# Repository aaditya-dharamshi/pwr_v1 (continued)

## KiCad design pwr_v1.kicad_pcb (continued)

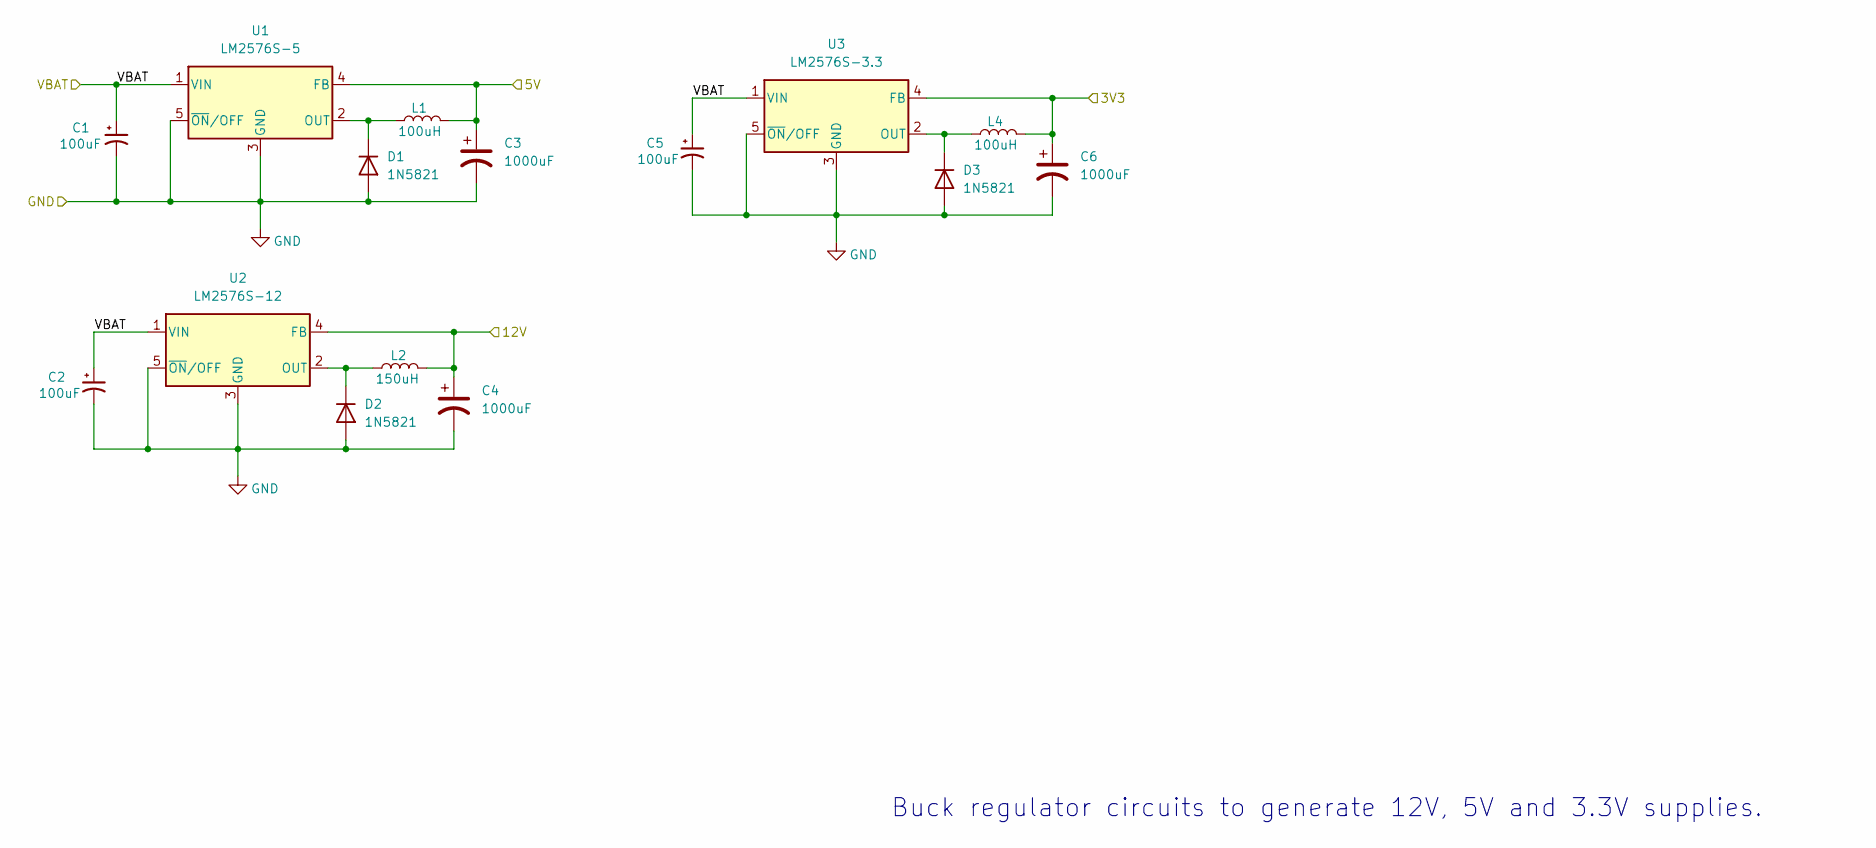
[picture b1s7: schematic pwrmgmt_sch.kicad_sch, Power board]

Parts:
C1, C2, C5: 100uF; CP_Elec_8x10
C3: 1000uF; CP_Elec_8x10.5
C4, C6: 1000uF; CP_Elec_10x10.5
D1, D2, D3: 1N5821; D_DO-201AD_P15.24mm_Horizontal
L1, L4: 100uH; L_Sunlord_MWSA1206S-101
L2: 150uH; L_TaiTech_TMPC1265_13.5x12.5mm
U1: LM2576S-5; TO-263-5_TabPin3
U2: LM2576S-12; TO-263-5_TabPin3
U3: LM2576S-3.3; TO-263-5_TabPin3

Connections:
3V3: C6.1, L4.2, U3.4 (FB); also elsewhere on the board
5V: C3.1, L1.2, U1.4 (FB); also elsewhere on the board
12V: C4.1, L2.2, U2.4 (FB); also elsewhere on the board
GND: C1.2, C2.2, C3.2, C4.2, C5.2, C6.2, D1.2 (A), D2.2 (A), D3.2 (A), U1.3 (GND), U1.5 (~ON/OFF), U2.3 (GND), U2.5 (~ON/OFF), U3.3 (GND), U3.5 (~ON/OFF); also elsewhere on the board
unnamed: D1.1 (K), L1.1, U1.2 (OUT)
unnamed: D2.1 (K), L2.1, U2.2 (OUT)
unnamed: D3.1 (K), L4.1, U3.2 (OUT)
VBAT: C1.1, C2.1, C5.1, U1.1 (VIN), U2.1 (VIN), U3.1 (VIN); also elsewhere on the board

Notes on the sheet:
Buck regulator circuits to generate 12V, 5V and 3.3V supplies.

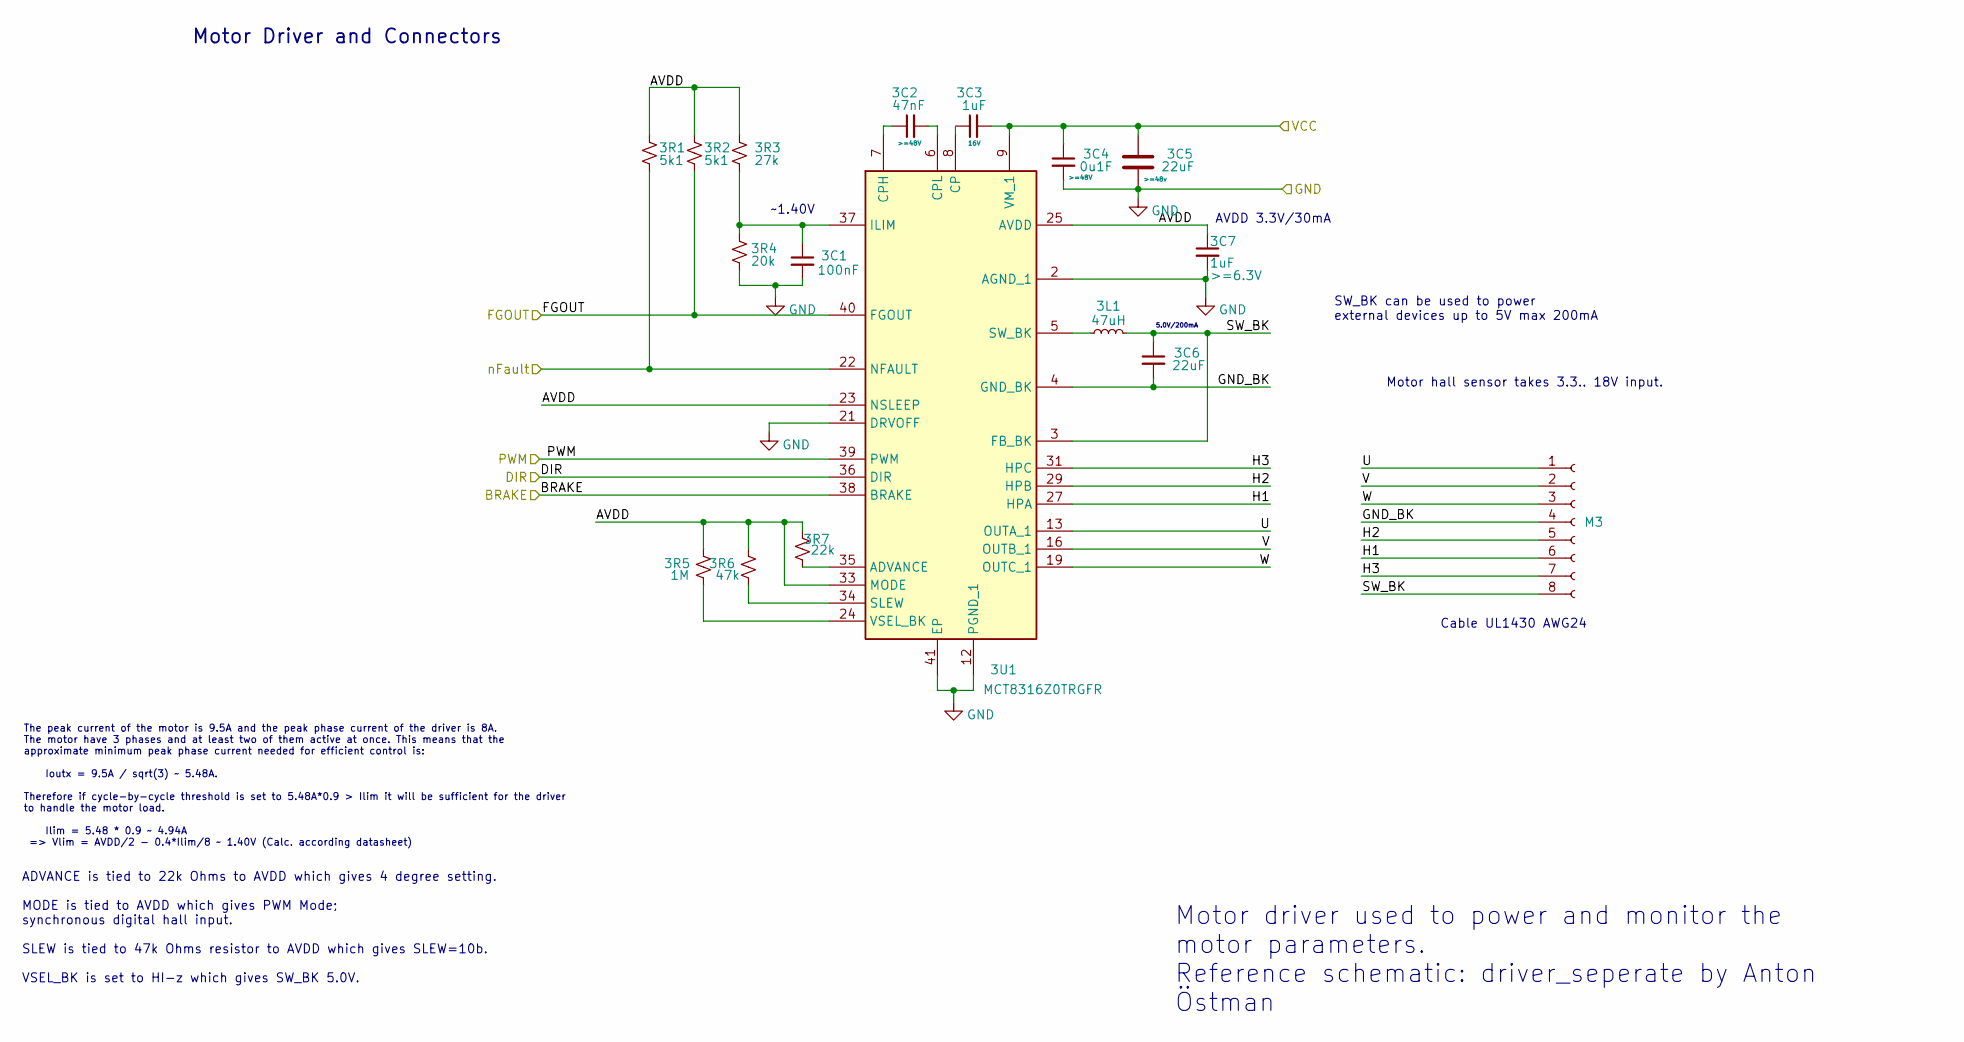
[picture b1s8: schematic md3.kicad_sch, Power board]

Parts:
3C1: 100nF; C_0402_1005Metric
3C2: 47nF; C_0402_1005Metric; Voltage >=48V
3C3: 1uF; C_0402_1005Metric; Voltage 16V
3C4: 0u1F; C_0402_1005Metric; Voltage >=48V
3C5: 22uF; C_2220_5750Metric; Voltage >=48v
3C6: 22uF; C_0402_1005Metric
3C7: 1uF; C_0402_1005Metric; Voltage >=6.3V
3L1: 47uH; L_0805_2012Metric
3R1, 3R2: 5k1; R_0603_1608Metric
3R3: 27k; R_0603_1608Metric
3R4: 20k; R_0603_1608Metric
3R5: 1M; R_0805_2012Metric
3R6: 47k; R_0402_1005Metric
3R7: 22k; R_0402_1005Metric
3U1: MCT8316Z0TRGFR; RGF0040E-IPC_B; Mouser Part Number 595-CT8316Z0TQRGFRQ1
M3: Conn_01x08_Socket; PinHeader_1x08_P2.54mm_Vertical

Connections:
5V: 3R1.2, 3U1.22 (NFAULT); also elsewhere on the board
/MotorDriver3/AVDD: 3C7.1, 3R1.1, 3R2.1, 3R3.1, 3R5.2, 3R6.2, 3R7.2, 3U1.23 (NSLEEP), 3U1.25 (AVDD), 3U1.33 (MODE)
/MotorDriver3/BRAKE: 3U1.38 (BRAKE); also elsewhere on the board
/MotorDriver3/DIR: 3U1.36 (DIR); also elsewhere on the board
/MotorDriver3/FGOUT: 3R2.2, 3U1.40 (FGOUT); also elsewhere on the board
/MotorDriver3/GND_BK: 3C6.2, 3U1.4 (GND_BK), M3.4
/MotorDriver3/H1: 3U1.27 (HPA), M3.6
/MotorDriver3/H2: 3U1.29 (HPB), M3.5
/MotorDriver3/H3: 3U1.31 (HPC), M3.7
/MotorDriver3/PWM: 3U1.39 (PWM); also elsewhere on the board
/MotorDriver3/SW_BK: 3C6.1, 3L1.2, 3U1.3 (FB_BK), M3.8
/MotorDriver3/U: 3U1.13 (OUTA_1), 3U1.14 (OUTA_2), M3.1
/MotorDriver3/V: 3U1.16 (OUTB_1), 3U1.17 (OUTB_2), M3.2
/MotorDriver3/W: 3U1.19 (OUTC_1), 3U1.20 (OUTC_2), M3.3
GND: 3C1.2, 3C4.2, 3C5.2, 3C7.2, 3R4.2, 3U1.2 (AGND_1), 3U1.12 (PGND_1), 3U1.15 (PGND_2), 3U1.18 (PGND_3), 3U1.21 (DRVOFF), 3U1.26 (AGND_2), 3U1.41 (EP); also elsewhere on the board
unnamed: 3R7.1, 3U1.35 (ADVANCE)
unnamed: 3C3.1, 3U1.8 (CP)
unnamed: 3C2.1, 3U1.7 (CPH)
unnamed: 3C2.2, 3U1.6 (CPL)
unnamed: 3C1.1, 3R3.2, 3R4.1, 3U1.37 (ILIM)
unnamed: 3R6.1, 3U1.34 (SLEW)
unnamed: 3L1.1, 3U1.5 (SW_BK)
unnamed: 3R5.1, 3U1.24 (VSEL_BK)
VBAT: 3C3.2, 3C4.1, 3C5.1, 3U1.9 (VM_1), 3U1.10 (VM_2), 3U1.11 (VM_3); also elsewhere on the board

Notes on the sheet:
5.0V/200mA
ADVANCE is tied to 22k Ohms to AVDD which gives 4 degree setting. MODE is tied to AVDD which gives PWM Mode; synchronous digital hall input. SLEW is tied to 47k Ohms resistor to AVDD which gives SLEW=10b. VSEL_BK is set to HI-z which gives SW_BK 5.0V.
Cable UL1430 AWG24
The peak current of the motor is 9.5A and the peak phase current of the driver is 8A. The motor have 3 phases and at least two of them active at once. This means that the approximate minimum peak phase current needed for efficient control is: Ioutx = 9.5A / sqrt(3) ~ 5.48A. Therefore if cycle-by-cy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
Motor hall sensor takes 3.3.. 18V input.
~1.40V
AVDD 3.3V/30mA
SW_BK can be used to power external devices up to 5V max 200mA
Motor Driver and Connectors
Motor driver used to power and monitor the motor parameters. Reference schematic: driver_seperate by Anton Östman

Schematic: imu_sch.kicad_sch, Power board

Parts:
C12, C13: 100nF; C_0402_1005Metric
R2, R3: 1k; R_0603_1608Metric
U4: LSM6DSLTR; LGA-14_3x2.5mm_P0.5mm_LayoutBorder3x4y

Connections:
3V3: C12.1, C13.1, R2.1, R3.1, U4.5 (VDDIO), U4.8 (VDD); also elsewhere on the board
/IMU/CS: U4.12 (CS); also elsewhere on the board
/IMU/INT1: U4.4 (INT1); also elsewhere on the board
/IMU/INT2: U4.9 (INT2); also elsewhere on the board
/IMU/SCL: R2.2, U4.13 (SCL); also elsewhere on the board
/IMU/SDA: R3.2, U4.14 (SDA); also elsewhere on the board
/IMU/SDO_SAO: U4.1 (SDO/SA0); also elsewhere on the board
GND: C12.2, C13.2, U4.2 (SDX), U4.3 (SCX), U4.6 (GND), U4.7 (GND); also elsewhere on the board

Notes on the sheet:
CS-0 : SPI mode CS-1 : I2C mode
IMU unit used to measure various motion parameters. Reference schematic: imu_LSM6DSL by Li Ang Hu

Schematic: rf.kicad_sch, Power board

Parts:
J_RF1: Conn_02x04_Counter_Clockwise; PinSocket_2x04_P2.54mm_Vertical

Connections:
3V3: J_RF1.8; also elsewhere on the board
/RF/CE: J_RF1.2; also elsewhere on the board
/RF/CSN: J_RF1.7; also elsewhere on the board
/RF/IRQ: J_RF1.5; also elsewhere on the board
/RF/MISO: J_RF1.4; also elsewhere on the board
/RF/MOSI: J_RF1.6; also elsewhere on the board
/RF/SCK: J_RF1.3; also elsewhere on the board
GND: J_RF1.1; also elsewhere on the board

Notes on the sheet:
RF Module socket

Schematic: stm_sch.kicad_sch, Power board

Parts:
CN11, CN12: Conn_02x36_Odd_Even; PinHeader_2x36_P2.54mm_Vertical_SMD

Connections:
5V: CN11.6; also elsewhere on the board
/Battery Supervisor/M: CN12.65; also elsewhere on the board
/Battery Supervisor/O1: CN11.11; also elsewhere on the board
/Battery Supervisor/O2: CN11.56; also elsewhere on the board
/Battery Supervisor/O3: CN11.54; also elsewhere on the board
/Battery Supervisor/O4: CN11.9; also elsewhere on the board
/Battery Supervisor/O5: CN12.42; also elsewhere on the board
/Battery Supervisor/O6: CN11.38; also elsewhere on the board
/STM32/CE_NRF: CN12.4; also elsewhere on the board
/STM32/CS_NRF: CN12.3; also elsewhere on the board
/STM32/IR_CS: CN11.30; also elsewhere on the board
/STM32/IR_IN: CN12.12; also elsewhere on the board
/STM32/IR_INT1: CN12.35; also elsewhere on the board
/STM32/IR_INT2: CN12.37; also elsewhere on the board
/STM32/IR_OUT: CN12.14; also elsewhere on the board
/STM32/KICKER_CHARGE: CN12.18; also elsewhere on the board
/STM32/KICKER_CS: CN12.49; also elsewhere on the board
/STM32/KICKER_DISCHARGE1: CN12.25; also elsewhere on the board
/STM32/KICKER_DISCHARGE2: CN12.16; also elsewhere on the board
/STM32/KICKER_ERR: CN12.30; also elsewhere on the board
/STM32/MISO: CN12.13; also elsewhere on the board
/STM32/MOSI: CN12.29; also elsewhere on the board
/STM32/MOTOR1_BREAK: CN12.22; also elsewhere on the board
/STM32/MOTOR1_ENCODER: CN11.4; also elsewhere on the board
/STM32/MOTOR1_PWM: CN12.52; also elsewhere on the board
/STM32/MOTOR1_REVERSE: CN12.17; also elsewhere on the board
/STM32/MOTOR2_BREAK: CN12.41; also elsewhere on the board
/STM32/MOTOR2_ENCODER: CN12.64; also elsewhere on the board
/STM32/MOTOR2_PWM: CN12.56; also elsewhere on the board
/STM32/MOTOR2_REVERSE: CN12.40; also elsewhere on the board
/STM32/MOTOR3_BREAK: CN12.43; also elsewhere on the board
/STM32/MOTOR3_ENCODER: CN11.32; also elsewhere on the board
/STM32/MOTOR3_PWM: CN12.55; also elsewhere on the board
/STM32/MOTOR3_REVERSE: CN12.44; also elsewhere on the board
/STM32/MOTOR4_BREAK: CN11.46; also elsewhere on the board
/STM32/MOTOR4_ENCODER: CN11.28; also elsewhere on the board
/STM32/MOTOR4_PWM: CN12.51; also elsewhere on the board
/STM32/MOTOR4_REVERSE: CN12.53; also elsewhere on the board
/STM32/MOTOR5_BREAK: CN11.62; also elsewhere on the board
/STM32/MOTOR5_ENCODER: CN11.17; also elsewhere on the board
/STM32/MOTOR5_PWM: CN11.50; also elsewhere on the board
/STM32/MOTOR5_REVERSE: CN11.48; also elsewhere on the board
/STM32/NRF_IRQ: CN12.26; also elsewhere on the board
/STM32/SCK: CN12.11; also elsewhere on the board
GND: CN11.8, CN11.19, CN11.20, CN11.22, CN11.49, CN11.60, CN12.9, CN12.20, CN12.39, CN12.54, CN12.63; also elsewhere on the board

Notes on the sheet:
STM32 Nucleo H755ZI devboard connector
Nucleo pin mapping details

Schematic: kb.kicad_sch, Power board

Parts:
J1: Conn_01x12_Pin; CON12_1X12_UR_DF13
Q1: BSS84; SOT-23
RK1, RK2, RK3, RK4, RK5, RK6, RK7, RK8: 100; R_0402_1005Metric
RK9, RK10: 10k; R_0402_1005Metric

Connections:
3V3: J1.10, RK9.1, RK10.1; also elsewhere on the board
12V: J1.11; also elsewhere on the board
/KB/CHG: RK5.2; also elsewhere on the board
/KB/CLK: RK2.2; also elsewhere on the board
/KB/CS: Q1.1 (G), RK1.2; also elsewhere on the board
/KB/DIS1: RK6.2, RK9.2; also elsewhere on the board
/KB/DIS2: RK7.2, RK10.2; also elsewhere on the board
/KB/ERR: RK8.2; also elsewhere on the board
/KB/MISO: Q1.3 (D); also elsewhere on the board
/KB/MOSI: RK4.2; also elsewhere on the board
GND: J1.9; also elsewhere on the board
unnamed: J1.1, RK1.1
unnamed: J1.2, RK2.1
unnamed: J1.3, RK3.1
unnamed: J1.4, RK4.1
unnamed: J1.5, RK5.1
unnamed: J1.6, RK6.1
unnamed: J1.7, RK7.1
unnamed: J1.8, RK8.1
unnamed: Q1.2 (S), RK3.2
VBAT: J1.12; also elsewhere on the board

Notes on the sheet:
Kicker board connector

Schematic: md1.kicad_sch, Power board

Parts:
1C1: 100nF; C_0402_1005Metric
1C2: 47nF; C_0402_1005Metric; Voltage >=48V
1C3: 1uF; C_0402_1005Metric; Voltage 16V
1C4: 0u1F; C_0402_1005Metric; Voltage >=48V
1C5: 22uF; C_2220_5750Metric; Voltage >=48v
1C6: 22uF; C_0402_1005Metric
1C7: 1uF; C_0402_1005Metric; Voltage >=6.3V
1L1: 47uH; L_0805_2012Metric
1R1, 1R2: 5k1; R_0603_1608Metric
1R3: 27k; R_0603_1608Metric
1R4: 20k; R_0603_1608Metric
1R5: 1M; R_0805_2012Metric
1R6: 47k; R_0402_1005Metric
1R7: 22k; R_0402_1005Metric
1U1: MCT8316Z0TRGFR; RGF0040E-IPC_B; Mouser Part Number 595-CT8316Z0TQRGFRQ1
M1: Conn_01x08_Socket; PinHeader_1x08_P2.54mm_Vertical

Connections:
5V: 1R1.2, 1U1.22 (NFAULT); also elsewhere on the board
/MotorDriver1/AVDD: 1C7.1, 1R1.1, 1R2.1, 1R3.1, 1R5.2, 1R6.2, 1R7.2, 1U1.23 (NSLEEP), 1U1.25 (AVDD), 1U1.33 (MODE)
/MotorDriver1/BRAKE: 1U1.38 (BRAKE); also elsewhere on the board
/MotorDriver1/DIR: 1U1.36 (DIR); also elsewhere on the board
/MotorDriver1/FGOUT: 1R2.2, 1U1.40 (FGOUT); also elsewhere on the board
/MotorDriver1/GND_BK: 1C6.2, 1U1.4 (GND_BK), M1.4
/MotorDriver1/H1: 1U1.27 (HPA), M1.6
/MotorDriver1/H2: 1U1.29 (HPB), M1.5
/MotorDriver1/H3: 1U1.31 (HPC), M1.7
/MotorDriver1/PWM: 1U1.39 (PWM); also elsewhere on the board
/MotorDriver1/SW_BK: 1C6.1, 1L1.2, 1U1.3 (FB_BK), M1.8
/MotorDriver1/U: 1U1.13 (OUTA_1), 1U1.14 (OUTA_2), M1.1
/MotorDriver1/V: 1U1.16 (OUTB_1), 1U1.17 (OUTB_2), M1.2
/MotorDriver1/W: 1U1.19 (OUTC_1), 1U1.20 (OUTC_2), M1.3
GND: 1C1.2, 1C4.2, 1C5.2, 1C7.2, 1R4.2, 1U1.2 (AGND_1), 1U1.12 (PGND_1), 1U1.15 (PGND_2), 1U1.18 (PGND_3), 1U1.21 (DRVOFF), 1U1.26 (AGND_2), 1U1.41 (EP); also elsewhere on the board
unnamed: 1R7.1, 1U1.35 (ADVANCE)
unnamed: 1C3.1, 1U1.8 (CP)
unnamed: 1C2.1, 1U1.7 (CPH)
unnamed: 1C2.2, 1U1.6 (CPL)
unnamed: 1C1.1, 1R3.2, 1R4.1, 1U1.37 (ILIM)
unnamed: 1R6.1, 1U1.34 (SLEW)
unnamed: 1L1.1, 1U1.5 (SW_BK)
unnamed: 1R5.1, 1U1.24 (VSEL_BK)
VBAT: 1C3.2, 1C4.1, 1C5.1, 1U1.9 (VM_1), 1U1.10 (VM_2), 1U1.11 (VM_3); also elsewhere on the board

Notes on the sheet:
Motor hall sensor takes 3.3.. 18V input.
ADVANCE is tied to 22k Ohms to AVDD which gives 4 degree setting. MODE is tied to AVDD which gives PWM Mode; synchronous digital hall input. SLEW is tied to 47k Ohms resistor to AVDD which gives SLEW=10b. VSEL_BK is set to HI-z which gives SW_BK 5.0V.
The peak current of the motor is 9.5A and the peak phase current of the driver is 8A. The motor have 3 phases and at least two of them active at once. This means that the approximate minimum peak phase current needed for efficient control is: Ioutx = 9.5A / sqrt(3) ~ 5.48A. Therefore if cycle-by-cy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
~1.40V
Cable UL1430 AWG24
SW_BK can be used to power external devices up to 5V max 200mA
5.0V/200mA
Motor Driver and Connectors
AVDD 3.3V/30mA
Motor driver used to power and monitor the motor parameters. Reference schematic: driver_seperate by Anton Östman

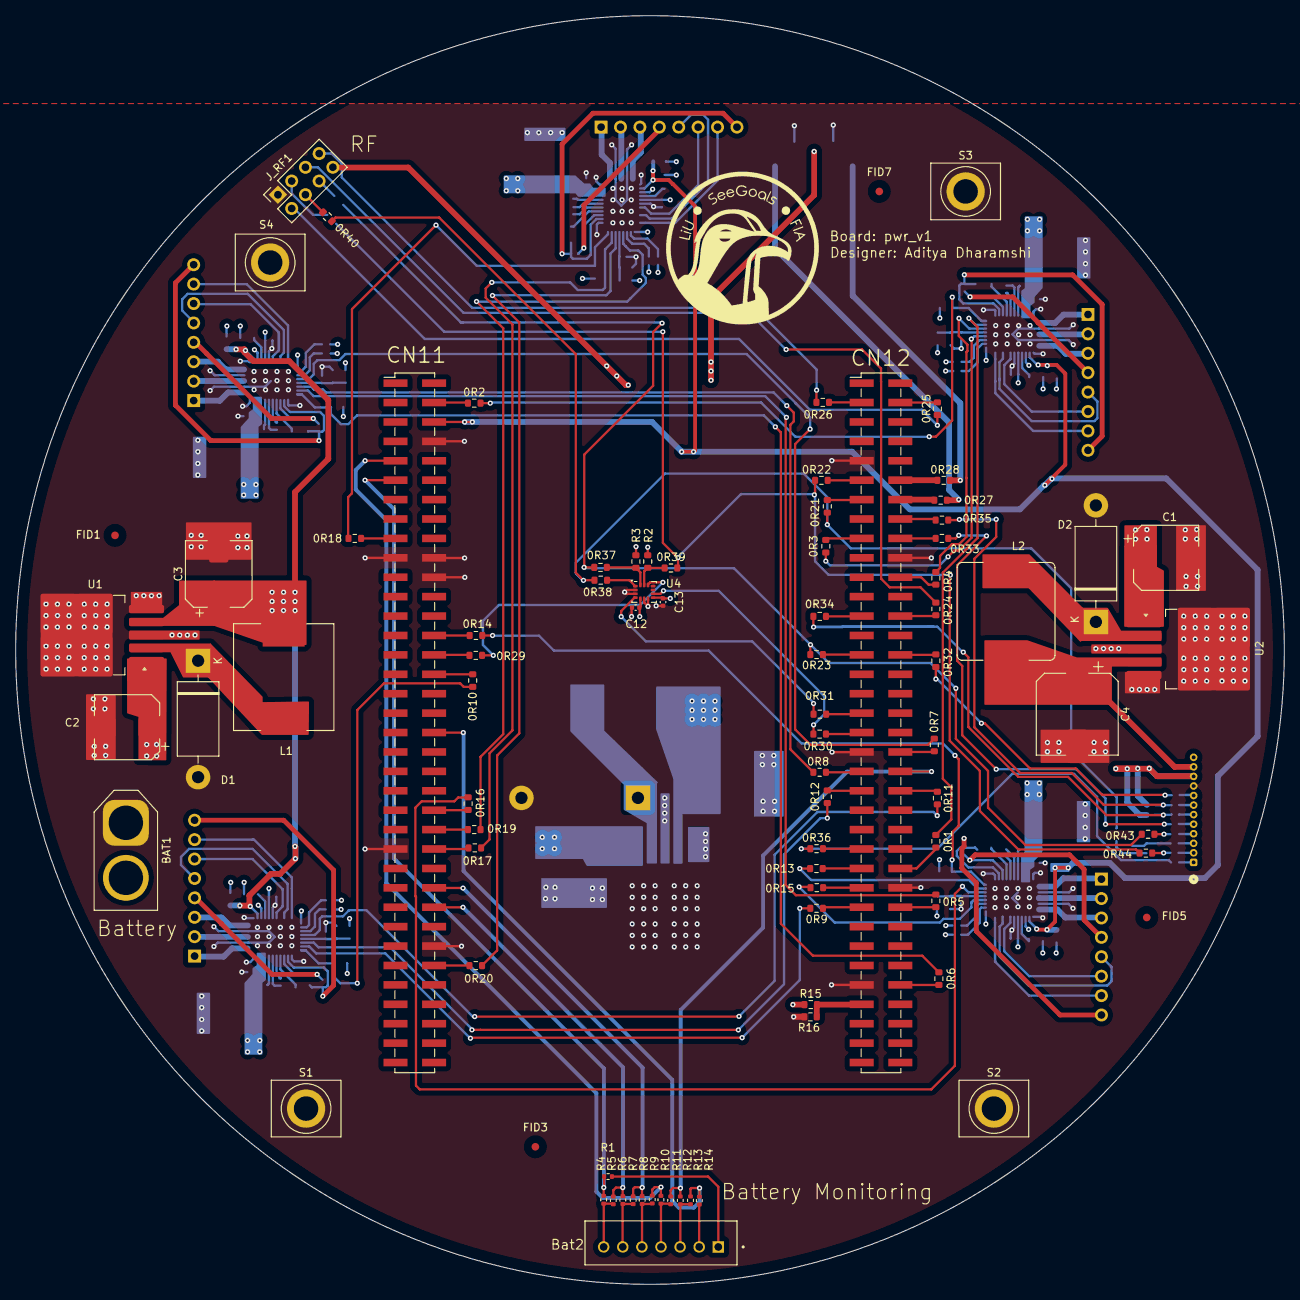
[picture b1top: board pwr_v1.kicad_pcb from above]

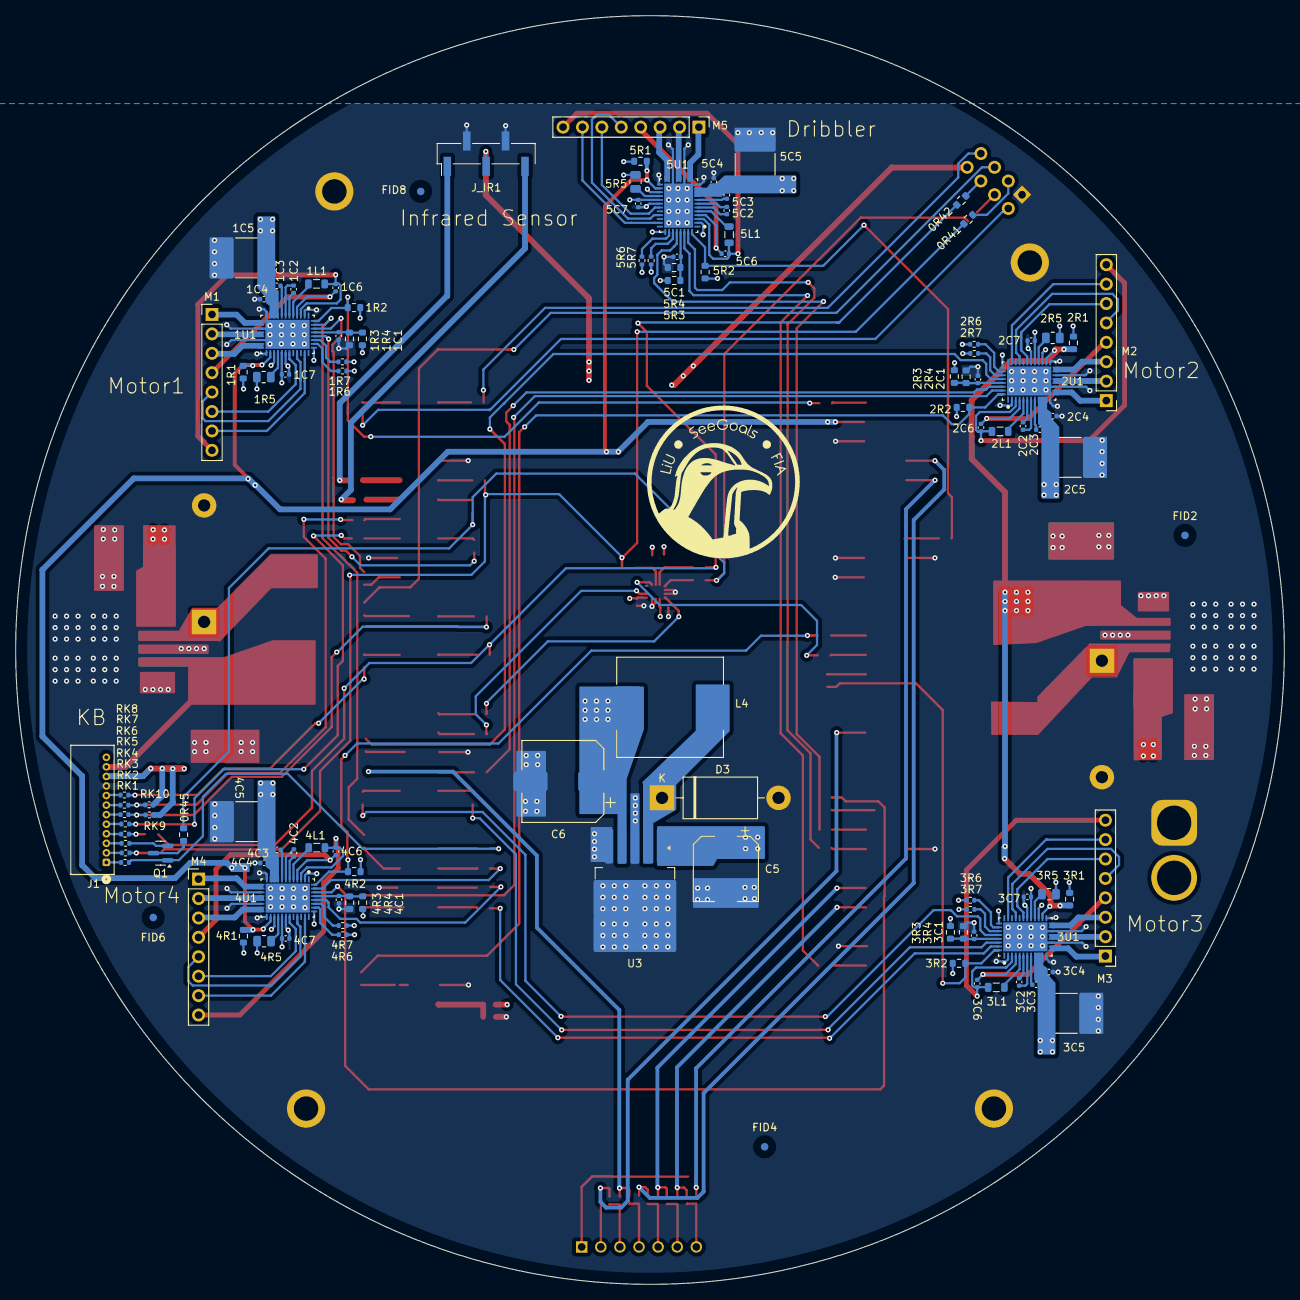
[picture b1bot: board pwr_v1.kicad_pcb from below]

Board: 4 copper layers, 166.0 x 166.0 mm, 194 parts (110 on the bottom side), 197 nets.

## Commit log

2026-03-02 Files uploaded
